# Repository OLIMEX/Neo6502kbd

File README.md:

# Neo6502kbd
Neo6502kbd is all in one Retro computer with 6502 processor, Keyboard, Four USB hosts and DVI/HDMI output.

With Reload emulator you can run Apple ][ and Oric Atmos emulators.

[Neo6502kbd-1](DOCUMENTS/Neo6502kbd-1.jpg)

https://www.olimex.com/Products/Retro-Computers/Neo6502kbd/open-source-hardware

## Licensee
* Hardware is released under CERN Open Hardware Licence Version 2 - Strongly Reciprocal
* Software is released under MIT Licensee
* Documentation is released under CC BY-SA 4.!

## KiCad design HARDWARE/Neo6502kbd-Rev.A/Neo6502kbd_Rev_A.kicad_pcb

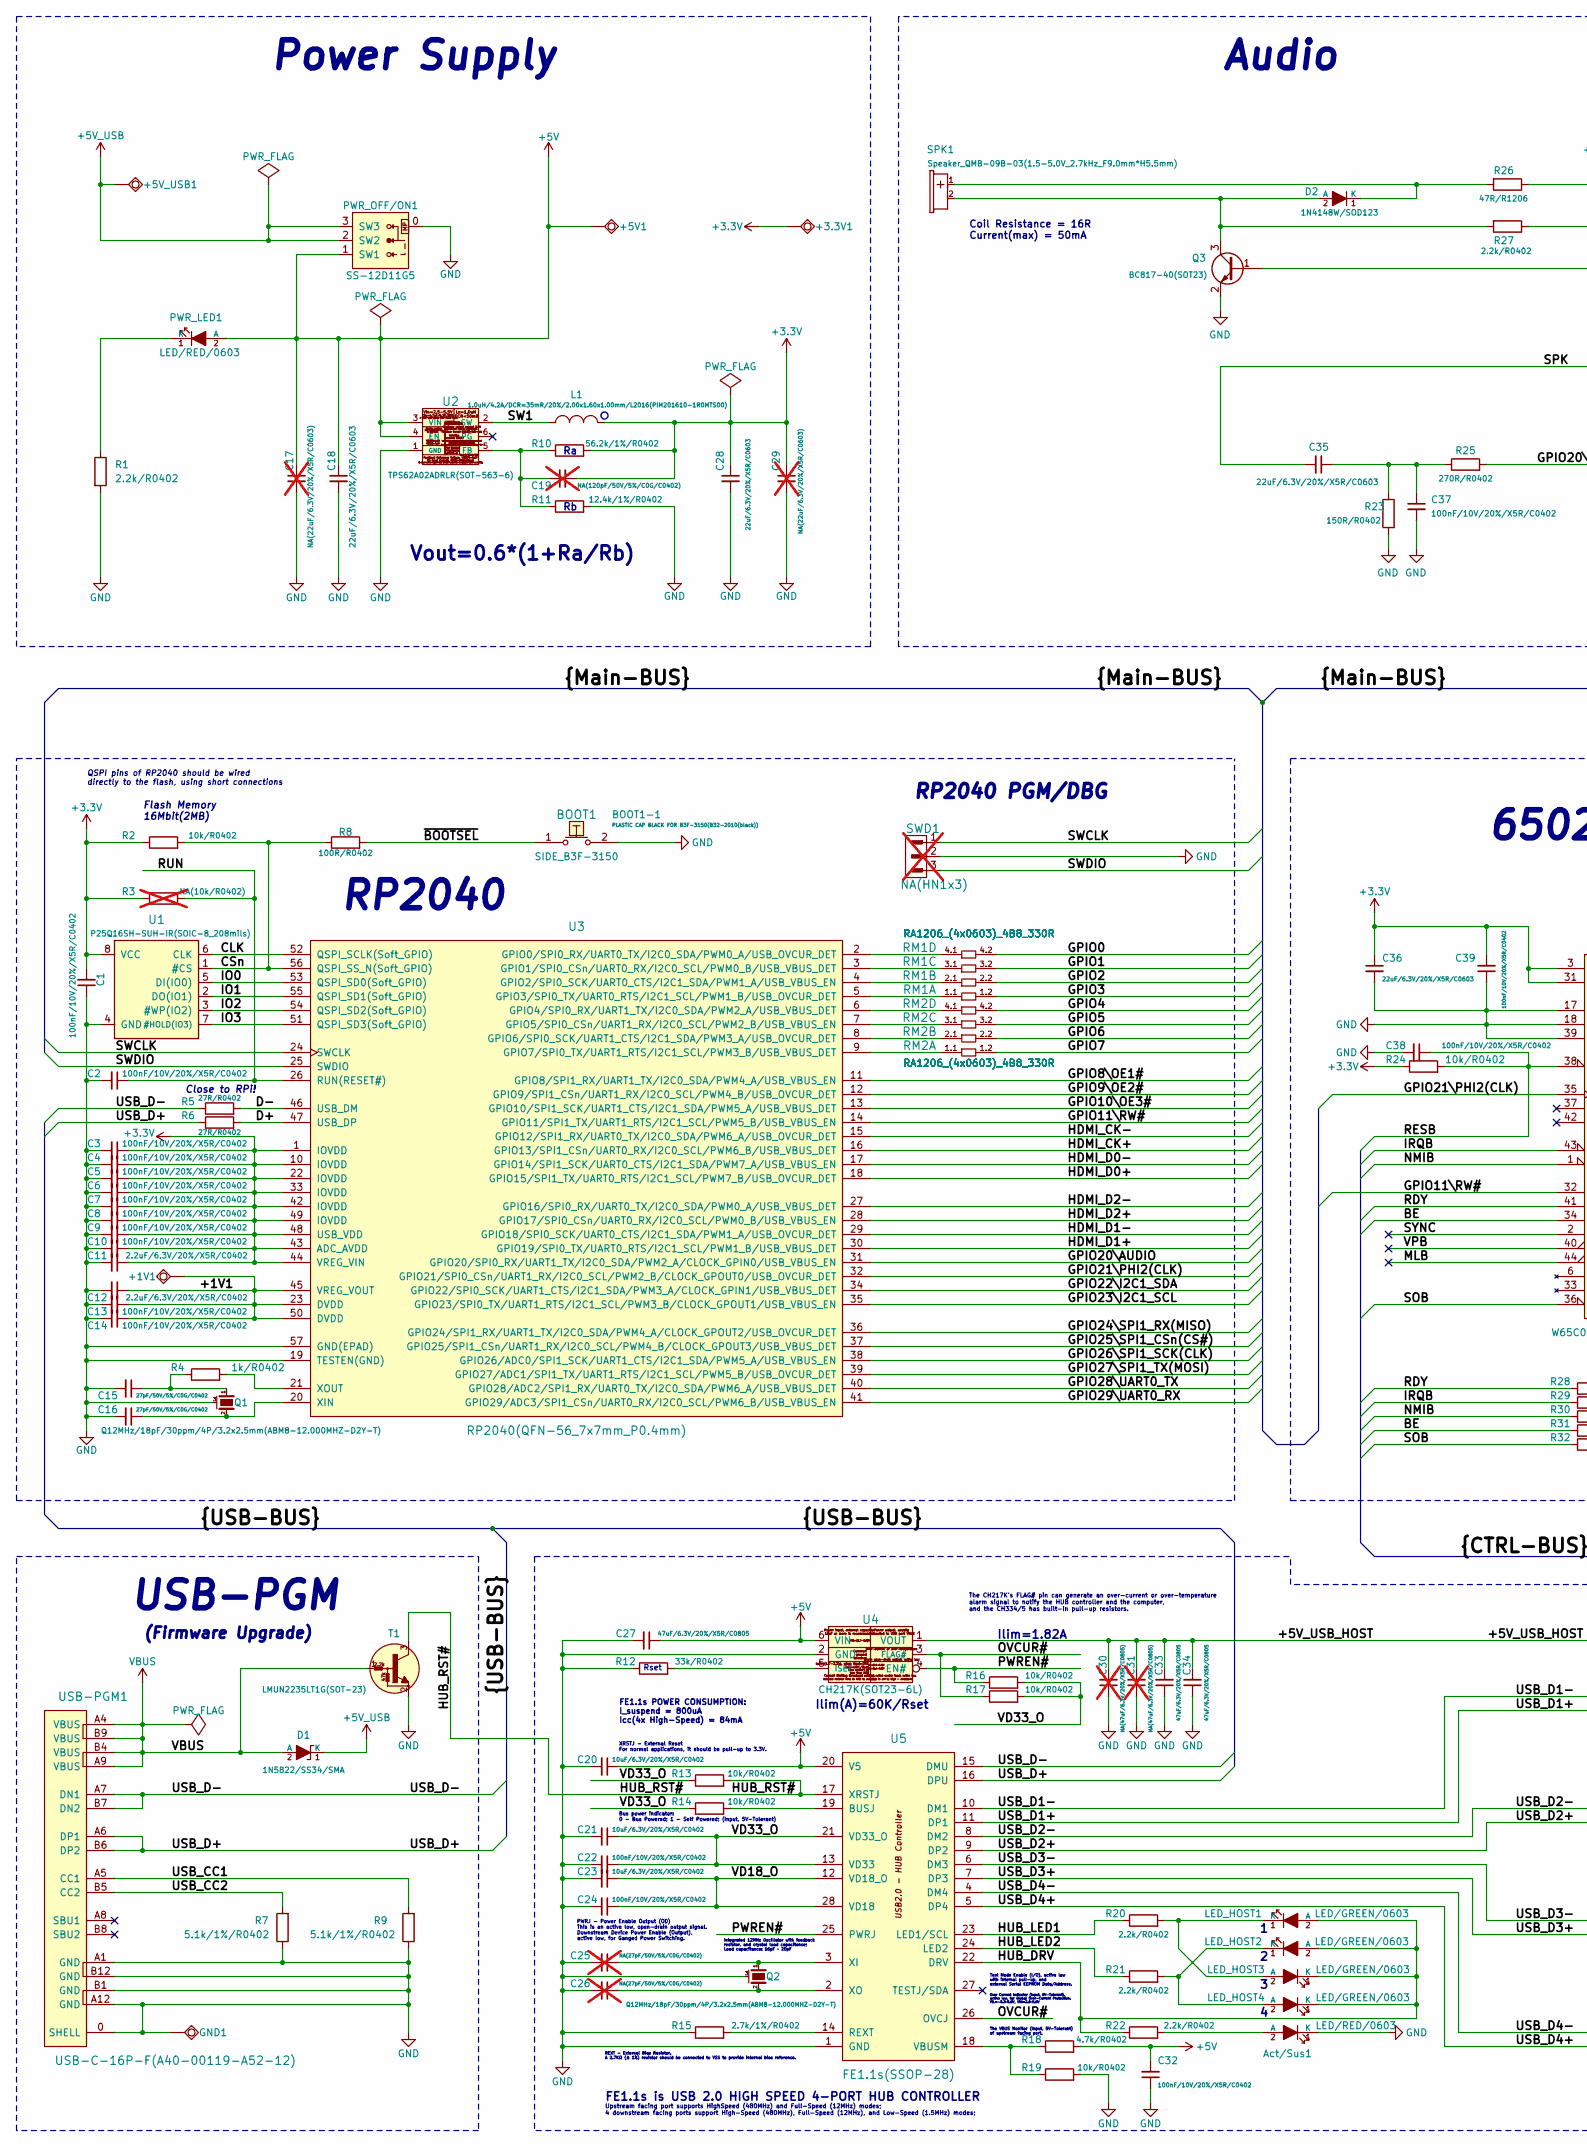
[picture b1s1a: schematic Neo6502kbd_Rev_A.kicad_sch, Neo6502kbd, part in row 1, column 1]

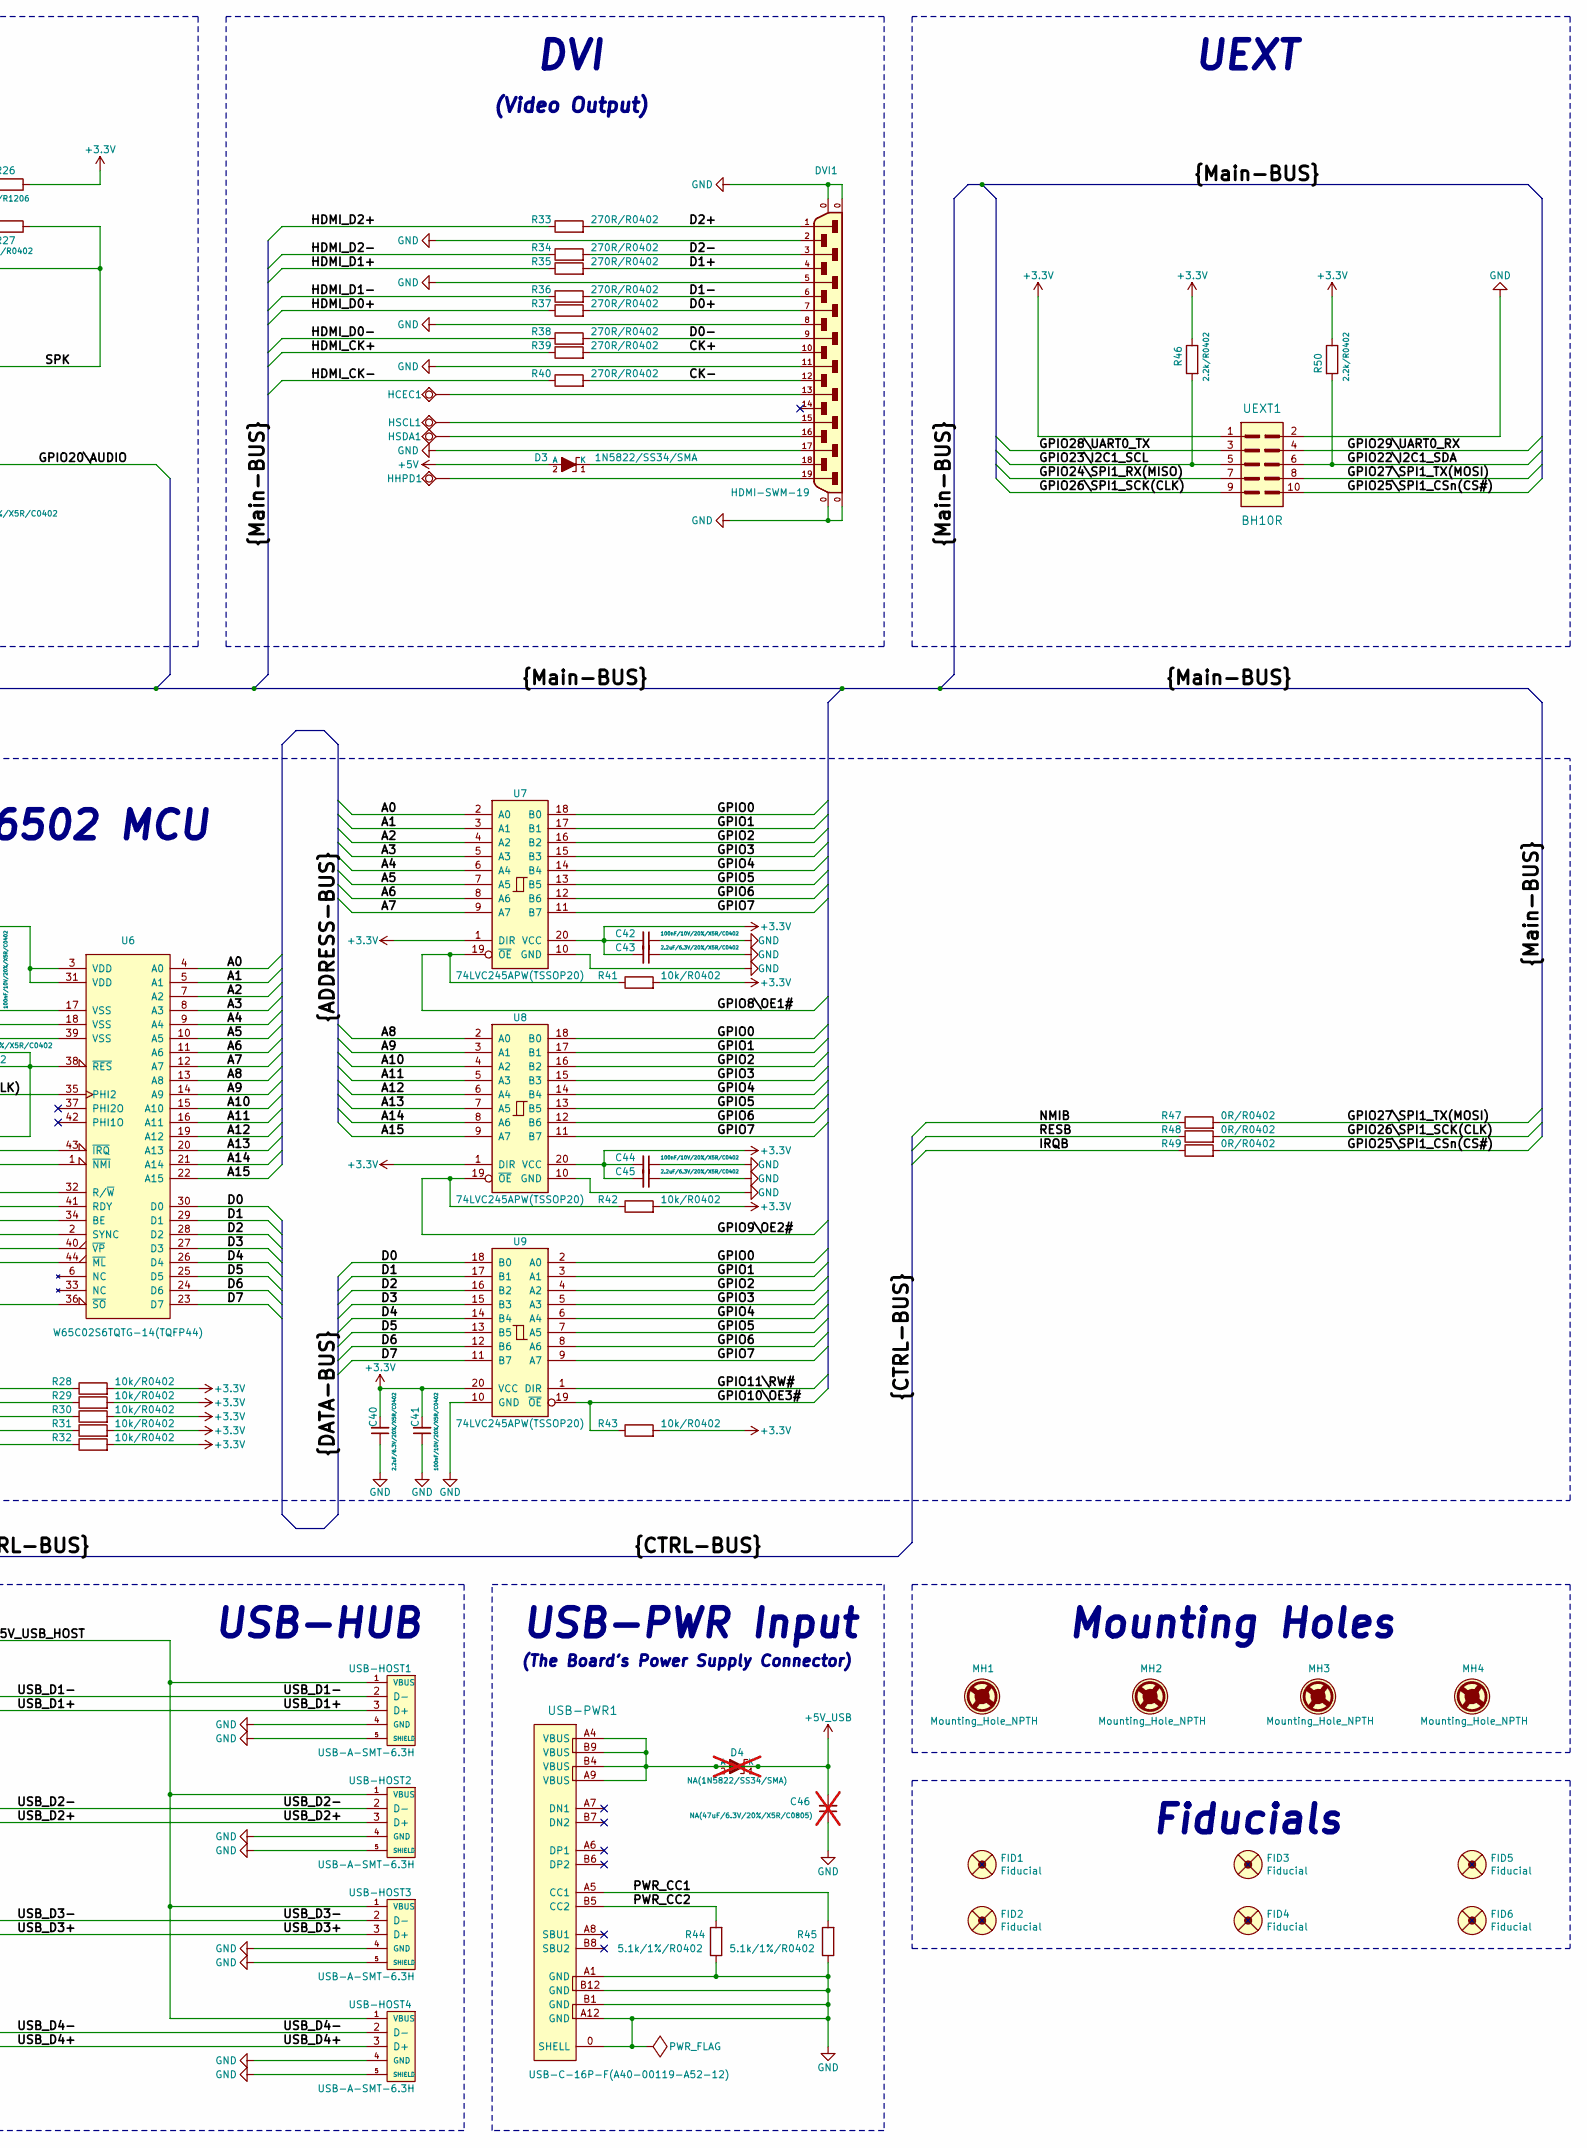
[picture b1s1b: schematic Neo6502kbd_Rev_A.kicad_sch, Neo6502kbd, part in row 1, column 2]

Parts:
+1V1, +3.3V1, +5V1, +5V_USB1: TESTPAD; TEST_PAD40x70_SQUARE
Act/Sus1: LED/RED/0603; LED_0603_KA
BOOT1: SIDE_B3F-3150; B3F-31XX
BOOT1-1: PLASTIC CAP BLACK FOR B3F-3150(B32-2010(black)); BUT-CAP_B32-2010(black)
C1, C2, C3, C4, C5, C6, C7, C8, C9, C10, C13, C14, C22, C24, C32, C37, C38, C39, C41, C42, C44: 100nF/10V/20%/X5R/C0402; C_0402_5MIL_DWS
C11, C12, C40, C43, C45: 2.2uF/6.3V/20%/X5R/C0402; C_0402_5MIL_DWS
C15, C16: 27pF/50V/5%/C0G/C0402; C_0402_5MIL_DWS
C17, C29: NA(22uF/6.3V/20%/X5R/C0603); C_0603_5MIL_DWS; not fitted
C18, C28, C35, C36: 22uF/6.3V/20%/X5R/C0603; C_0603_5MIL_DWS
C19: NA(120pF/50V/5%/C0G/C0402); C_0402_5MIL_DWS; not fitted
C20, C21, C23: 10uF/6.3V/20%/X5R/C0402; C_0402_5MIL_DWS
C25, C26: NA(27pF/50V/5%/C0G/C0402); C_0402_5MIL_DWS; not fitted
C27, C33, C34: 47uF/6.3V/20%/X5R/C0805; C_0805_5MIL_DWS
C30, C31, C46: NA(47uF/6.3V/20%/X5R/C0805); C_0805_5MIL_DWS; not fitted
D1, D3: 1N5822/SS34/SMA; SMA-KA
D2: 1N4148W/SOD123; SOD-123_1C-2A_KA
D4: NA(1N5822/SS34/SMA); SMA-KA; not fitted
DVI1: HDMI-SWM-19; HDMI-SWM-19_Paste
FID1, FID2, FID3: Fiducial; Fiducial1x3_Paste
FID4, FID5, FID6: Fiducial; Fiducial1x3
GND1: TESTPAD; TEST_PAD40x70_SQUARE
HCEC1: TESTPAD; TESTPAD_40-ROUND
HHPD1: TESTPAD; TESTPAD_40-ROUND
HSCL1: TESTPAD; TESTPAD_40-ROUND
HSDA1: TESTPAD; TESTPAD_40-ROUND
L1: 1.0uH/4.2A/DCR=35mR/20%/2.00x1.60x1.00mm/L2016(PI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; L_2016_MM
LED_HOST1, LED_HOST2, LED_HOST3, LED_HOST4: LED/GREEN/0603; LED_0603_KA
MH1, MH2, MH3, MH4: Mounting_Hole_NPTH; Mounting_Hole_Drill-3.3mm_Clerance-7mm
PWR_LED1: LED/RED/0603; LED_0603_KA
PWR_OFF/ON1: SS-12D11G5
Q1, Q2: Q12MHz/18pF/30ppm/4P/3.2x2.5mm(ABM8-12.000MHZ-D2Y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; TSX-3.2x2.5mm_GND(3)
Q3: BC817-40(SOT23); SOT23
R1, R20, R21, R22, R27, R46, R50: 2.2k/R0402; R_0402_5MIL_DWS
R2, R13, R14, R16, R17, R19, R24, R28, R29, R30, R31, R32, R41, R42, R43: 10k/R0402; R_0402_5MIL_DWS
R3: NA(10k/R0402); R_0402_5MIL_DWS; not fitted
R4: 1k/R0402; R_0402_5MIL_DWS
R5, R6: 27R/R0402; R_0402_5MIL_DWS
R7, R9, R44, R45: 5.1k/1%/R0402; R_0402_5MIL_DWS
R8: 100R/R0402; R_0402_5MIL_DWS
R10: 56.2k/1%/R0402; R_0402_5MIL_DWS
R11: 12.4k/1%/R0402; R_0402_5MIL_DWS
R12: 33k/R0402; R_0402_5MIL_DWS
R15: 2.7k/1%/R0402; R_0402_5MIL_DWS
R18: 4.7k/R0402; R_0402_5MIL_DWS
R23: 150R/R0402; R_0402_5MIL_DWS
R25, R33, R34, R35, R36, R37, R38, R39, R40: 270R/R0402; R_0402_5MIL_DWS
R26: 47R/R1206; R_1206_5MIL_DWS
R47, R48, R49: 0R/R0402; R_0402_5MIL_DWS
RM1, RM2: RA1206_(4x0603)_4B8_330R; RA1206_(4X0603)_4B8_xx
SPK1: Speaker_QMB-09B-03(1.5-5.0V_2.7kHz_F9.0mm*H5.5mm); Speaker_QMB-09B-03_1-Plus_2-Minus
SWD1: NA(HN1x3); HN1x3; not fitted
T1: LMUN2235LT1G(SOT-23); SOT23
U1: P25Q16SH-SUH-IR(SOIC-8_208mils); SO-8_208mil
U2: TPS62A02ADRLR(SOT-563-6); SOT-563-6
U3: RP2040(QFN-56_7x7mm_P0.4mm); QFN56_7x7_Pitch_0.4mm
U4: CH217K(SOT23-6L); SOT23-6
U5: FE1.1s(SSOP-28); SSOP28_10x4mm_Pitch_0.64mm
U6: W65C02S6TQTG-14(TQFP44); TQFP44_NEO6502
U7, U8, U9: 74LVC245APW(TSSOP20); TSSOP20_Pitch-0.65mm_6.6x4.5x1.2mm
UEXT1: BH10R
USB-HOST1, USB-HOST2, USB-HOST3, USB-HOST4: USB-A-SMT-6.3H; USB-A-SMT-6.3H_HOST_Female
USB-PGM1: USB-C-16P-F(A40-00119-A52-12); USB2.0_TYPE-C(A40-00119-A52-12)_Paste
USB-PWR1: USB-C-16P-F(A40-00119-A52-12); USB2.0_TYPE-C(A40-00119-A52-12)_Paste

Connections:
+3.3V: +3.3V1.1 (Pad), C1.2, C3.1, C4.1, C5.1, C6.1, C7.1, C8.1, C9.1, C10.1, C11.1, C19.2, C28.1, C29.1, C36.1, C39.2, C40.2, C41.2, C42.2, C43.2, C44.2, C45.2, L1.2, R2.1, R3.1, R10.2, R24.1, R26.1, R28.2, R29.2, R30.2, R31.2, R32.2, R41.2, R42.2, R43.2, R46.1, R50.1, U1.8 (VCC), U3.1 (IOVDD), U3.10 (IOVDD), U3.22 (IOVDD), U3.33 (IOVDD), U3.42 (IOVDD), U3.43 (ADC_AVDD), U3.44 (VREG_VIN), U3.48 (USB_VDD), U3.49 (IOVDD), U6.3 (VDD), U6.31 (VDD), U7.1 (DIR), U7.20 (VCC), U8.1 (DIR), U8.20 (VCC), U9.20 (VCC), UEXT1.1
+5V: +5V1.1 (Pad), C17.1, C18.1, C20.1, C27.1, C32.2, D3.2 (A), PWR_LED1.2 (A), PWR_OFF/ON1.1 (SW1), R18.2, U2.3 (VIN), U2.4 (EN), U4.6 (VIN), U5.20 (V5)
+5V_USB: +5V_USB1.1 (Pad), C46.2, D1.1 (K), D4.1 (K), D4.2 (A), PWR_OFF/ON1.2 (SW2), PWR_OFF/ON1.3 (SW3), USB-PWR1.A4 (VBUS), USB-PWR1.A9 (VBUS), USB-PWR1.B4 (VBUS), USB-PWR1.B9 (VBUS)
/+1V1: +1V1.1 (Pad), C12.1, C13.1, C14.1, U3.23 (DVDD), U3.45 (VREG_VOUT), U3.50 (DVDD)
/+5V_USB_HOST: C30.2, C31.2, C33.2, C34.2, U4.1 (VOUT), USB-HOST1.1 (VBUS), USB-HOST2.1 (VBUS), USB-HOST3.1 (VBUS), USB-HOST4.1 (VBUS)
/A0: U6.4 (A0), U7.2 (A0)
/A1: U6.5 (A1), U7.3 (A1)
/A2: U6.7 (A2), U7.4 (A2)
/A3: U6.8 (A3), U7.5 (A3)
/A4: U6.9 (A4), U7.6 (A4)
/A5: U6.10 (A5), U7.7 (A5)
/A6: U6.11 (A6), U7.8 (A6)
/A7: U6.12 (A7), U7.9 (A7)
/A8: U6.13 (A8), U8.2 (A0)
/A9: U6.14 (A9), U8.3 (A1)
/A10: U6.15 (A10), U8.4 (A2)
/A11: U6.16 (A11), U8.5 (A3)
/A12: U6.19 (A12), U8.6 (A4)
/A13: U6.20 (A13), U8.7 (A5)
/A14: U6.21 (A14), U8.8 (A6)
/A15: U6.22 (A15), U8.9 (A7)
/BE: R31.1, U6.34 (BE)
/CK+: DVI1.10, R39.2
/CK-: DVI1.12, R40.2
/CLK: U1.6 (CLK), U3.52 (QSPI_SCLK(Soft_GPIO))
/CSn: R2.2, R8.1, U1.1 (#CS), U3.56 (QSPI_SS_N(Soft_GPIO))
/D0: U6.30 (D0), U9.18 (B0)
/D0+: DVI1.7, R37.2
/D0-: DVI1.9, R38.2
/D1: U6.29 (D1), U9.17 (B1)
/D1+: DVI1.4, R35.2
/D1-: DVI1.6, R36.2
/D2: U6.28 (D2), U9.16 (B2)
/D2+: DVI1.1, R33.2
/D2-: DVI1.3, R34.2
/D3: U6.27 (D3), U9.15 (B3)
/D4: U6.26 (D4), U9.14 (B4)
/D5: U6.25 (D5), U9.13 (B5)
/D6: U6.24 (D6), U9.12 (B6)
/D7: U6.23 (D7), U9.11 (B7)
/D+: R6.2, U3.47 (USB_DP)
/D-: R5.2, U3.46 (USB_DM)
/GPIO0: RM1.4.2, U7.18 (B0), U8.18 (B0), U9.2 (A0)
/GPIO1: RM1.3.2, U7.17 (B1), U8.17 (B1), U9.3 (A1)
/GPIO2: RM1.2.2, U7.16 (B2), U8.16 (B2), U9.4 (A2)
/GPIO3: RM1.1.2, U7.15 (B3), U8.15 (B3), U9.5 (A3)
/GPIO4: RM2.4.2, U7.14 (B4), U8.14 (B4), U9.6 (A4)
/GPIO5: RM2.3.2, U7.13 (B5), U8.13 (B5), U9.7 (A5)
/GPIO6: RM2.2.2, U7.12 (B6), U8.12 (B6), U9.8 (A6)
/GPIO7: RM2.1.2, U7.11 (B7), U8.11 (B7), U9.9 (A7)
/GPIO8\OE1#: R41.1, U3.11 (GPIO8/SPI1_RX/UART1_TX/I2C0_SDA/PWM4_A/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), U7.19 (~OE)
/GPIO9\OE2#: R42.1, U3.12 (GPIO9/SPI1_CSn/UART1_RX/I2C0_SCL/PWM4_B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), U8.19 (~OE)
/GPIO10\OE3#: R43.1, U3.13 (GPIO10/SPI1_SCK/UART1_CTS/I2C1_SDA/PWM5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), U9.19 (~OE)
/GPIO11\RW#: U3.14 (GPIO11/SPI1_TX/UART1_RTS/I2C1_SCL/PWM5_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), U6.32 (R/~W), U9.1 (DIR)
/GPIO20\AUDIO: R25.2, U3.31 (GPIO20/SPI0_RX/UART1_TX/I2C0_SDA/PWM2_A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)
/GPIO21\PHI2(CLK): U3.32 (GPIO21/SPI0_CSn/UART1_RX/I2C0_SCL/PWM2_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), U6.35 (PHI2)
/GPIO22\I2C1_SDA: R50.2, U3.34 (GPIO22/SPI0_SCK/UART1_CTS/I2C1_SDA/PWM3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), UEXT1.6
/GPIO23\I2C1_SCL: R46.2, U3.35 (GPIO23/SPI0_TX/UART1_RTS/I2C1_SCL/PWM3_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), UEXT1.5
/GPIO24\SPI1_RX(MISO): U3.36 (GPIO24/SPI1_RX/UART1_TX/I2C0_SDA/PWM4_A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), UEXT1.7
/GPIO25\SPI1_CSn(CS#): R49.2, U3.37 (GPIO25/SPI1_CSn/UART1_RX/I2C0_SCL/PWM4_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), UEXT1.10
/GPIO26\SPI1_SCK(CLK): R48.2, U3.38 (GPIO26/ADC0/SPI1_SCK/UART1_CTS/I2C1_SDA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), UEXT1.9
/GPIO27\SPI1_TX(MOSI): R47.2, U3.39 (GPIO27/ADC1/SPI1_TX/UART1_RTS/I2C1_SCL/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), UEXT1.8
/GPIO28\UART0_TX: U3.40 (GPIO28/ADC2/SPI1_RX/UART0_TX/I2C0_SDA/P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), UEXT1.3
/GPIO29\UART0_RX: U3.41 (GPIO29/ADC3/SPI1_CSn/UART0_RX/I2C0_SCL/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), UEXT1.4
/HDMI_CK+: R39.1, U3.16 (GPIO13/SPI1_CSn/UART0_RX/I2C0_SCL/PWM6_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)
/HDMI_CK-: R40.1, U3.15 (GPIO12/SPI1_RX/UART0_TX/I2C0_SDA/PWM6_A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)
/HDMI_D0+: R37.1, U3.18 (GPIO15/SPI1_TX/UART0_RTS/I2C1_SCL/PWM7_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)
/HDMI_D0-: R38.1, U3.17 (GPIO14/SPI1_SCK/UART0_CTS/I2C1_SDA/PWM7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)
/HDMI_D1+: R35.1, U3.30 (GPIO19/SPI0_TX/UART0_RTS/I2C1_SCL/PWM1_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)
/HDMI_D1-: R36.1, U3.29 (GPIO18/SPI0_SCK/UART0_CTS/I2C1_SDA/PWM1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)
/HDMI_D2+: R33.1, U3.28 (GPIO17/SPI0_CSn/UART0_RX/I2C0_SCL/PWM0_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)
/HDMI_D2-: R34.1, U3.27 (GPIO16/SPI0_RX/UART0_TX/I2C0_SDA/PWM0_A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)
/HUB_DRV: LED_HOST1.2 (A), LED_HOST2.2 (A), LED_HOST3.1 (K), LED_HOST4.1 (K), R22.1, U5.22 (DRV)
/HUB_LED1: R20.1, U5.23 (LED1/SCL)
/HUB_LED2: R21.1, U5.24 (LED2)
/HUB_RST#: R13.2, T1.3 (C), U5.17 (XRSTJ)
/IO0: U1.5 (DI(IO0)), U3.53 (QSPI_SD0(Soft_GPIO))
/IO1: U1.2 (DO(IO1)), U3.55 (QSPI_SD1(Soft_GPIO))
/IO2: U1.3 (#WP(IO2)), U3.54 (QSPI_SD2(Soft_GPIO))
/IO3: U1.7 (#HOLD(IO3)), U3.51 (QSPI_SD3(Soft_GPIO))
/IRQB: R29.1, R49.1, U6.43 (~IRQ)
/MLB: U6.44 (~ML)
/NMIB: R30.1, R47.1, U6.1 (~NMI)
/OVCUR#: R17.1, U4.3 (FLAG#), U5.26 (OVCJ)
/PWREN#: R16.1, U4.4 (EN#), U5.25 (PWRJ)
/PWR_CC1: R45.2, USB-PWR1.A5 (CC1)
/PWR_CC2: R44.2, USB-PWR1.B5 (CC2)
/RDY: R28.1, U6.41 (RDY)
/RESB: C38.1, R24.2, R48.1, U6.38 (~RES)
/RUN: C2.1, R3.2, U3.26 (RUN(RESET#))
/SOB: R32.1, U6.36 (~SO)
/SPK: C35.2, Q3.1 (B), R27.1
/SW1: L1.1, U2.2 (SW)
/SWCLK: SWD1.1, U3.24 (SWCLK)
/SWDIO: SWD1.3, U3.25 (SWDIO)
/SYNC: U6.2 (SYNC)
/USB_CC1: R9.2, USB-PGM1.A5 (CC1)
/USB_CC2: R7.2, USB-PGM1.B5 (CC2)
/USB_D1+: U5.11 (DP1), USB-HOST1.3 (D+)
/USB_D1-: U5.10 (DM1), USB-HOST1.2 (D-)
/USB_D2+: U5.9 (DP2), USB-HOST2.3 (D+)
/USB_D2-: U5.8 (DM2), USB-HOST2.2 (D-)
/USB_D3+: U5.7 (DP3), USB-HOST3.3 (D+)
/USB_D3-: U5.6 (DM3), USB-HOST3.2 (D-)
/USB_D4+: U5.5 (DP4), USB-HOST4.3 (D+)
/USB_D4-: U5.4 (DM4), USB-HOST4.2 (D-)
/USB_D+: R6.1, U5.16 (DPU), USB-PGM1.A6 (DP1), USB-PGM1.B6 (DP2)
/USB_D-: R5.1, U5.15 (DMU), USB-PGM1.A7 (DN1), USB-PGM1.B7 (DN2)
/VD18_O: C23.1, C24.1, U5.12 (VD18_O), U5.28 (VD18)
/VD33_O: C21.1, C22.1, R13.1, R14.1, R16.2, R17.2, U5.13 (VD33), U5.21 (VD33_O)
/VPB: U6.40 (~VP)
/~BOOTSEL: BOOT1.1, R8.2
GND: Act/Sus1.1 (K), BOOT1.2, C1.1, C2.2, C3.2, C4.2, C5.2, C6.2, C7.2, C8.2, C9.2, C10.2, C11.2, C12.2, C13.2, C14.2, C15.2, C16.2, C17.2, C18.2, C20.2, C21.2, C22.2, C23.2, C24.2, C25.2, C26.2, C27.2, C28.2, C29.2, C30.1, C31.1, C32.1, C33.1, C34.1, C36.2, C37.2, C38.2, C39.1, C40.1, C41.1, C42.1, C43.1, C44.1, C45.1, C46.1, DVI1.0 (23), DVI1.2, DVI1.5, DVI1.8, DVI1.11, DVI1.17, GND1.1 (Pad), PWR_OFF/ON1.0, Q1.3 (case), Q2.3 (case), Q3.2 (E), R1.2, R7.1, R9.1, R11.2, R12.1, R15.1, R19.2, R23.2, R44.1, R45.1, SWD1.2, T1.2 (E), U1.4 (GND), U2.1 (GND), U3.19 (TESTEN(GND)), U3.57 (GND(EPAD)), U4.2 (GND), U5.1 (GND), U6.17 (VSS), U6.18 (VSS), U6.39 (VSS), U7.10 (GND), U8.10 (GND), U9.10 (GND), UEXT1.2, USB-HOST1.4 (GND), USB-HOST1.5 (SHIELD), USB-HOST2.4 (GND), USB-HOST2.5 (SHIELD), USB-HOST3.4 (GND), USB-HOST3.5 (SHIELD), USB-HOST4.4 (GND), USB-HOST4.5 (SHIELD), USB-PGM1.0 (SHELL), USB-PGM1.A1 (GND), USB-PGM1.A12 (GND), USB-PGM1.B1 (GND), USB-PGM1.B12 (GND), USB-PWR1.0 (SHELL), USB-PWR1.A1 (GND), USB-PWR1.A12 (GND), USB-PWR1.B1 (GND), USB-PWR1.B12 (GND)
unnamed: Act/Sus1.2 (A), R22.2
unnamed: C15.1, Q1.1, R4.1
unnamed: C35.1, C37.1, R23.1, R25.1
unnamed: D2.2 (A), Q3.3 (C), R27.2, SPK1.2 (MINUS)
unnamed: D2.1 (K), R26.2, SPK1.1 (PLUS)
unnamed: D3.1 (K), DVI1.18
unnamed: DVI1.13, HCEC1.1 (Pad)
unnamed: DVI1.15, HSCL1.1 (Pad)
unnamed: DVI1.16, HSDA1.1 (Pad)
unnamed: DVI1.19, HHPD1.1 (Pad)
unnamed: LED_HOST1.1 (K), LED_HOST3.2 (A), R20.2
unnamed: LED_HOST2.1 (K), LED_HOST4.2 (A), R21.2
unnamed: PWR_LED1.1 (K), R1.1
unnamed: C19.1, R10.1, R11.1, U2.5 (FB)
unnamed: RM1.4.1, U3.2 (GPIO0/SPI0_RX/UART0_TX/I2C0_SDA/PWM0_A/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)
unnamed: RM1.3.1, U3.3 (GPIO1/SPI0_CSn/UART0_RX/I2C0_SCL/PWM0_B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)
unnamed: RM1.2.1, U3.4 (GPIO2/SPI0_SCK/UART0_CTS/I2C1_SDA/PWM1_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)
unnamed: RM1.1.1, U3.5 (GPIO3/SPI0_TX/UART0_RTS/I2C1_SCL/PWM1_B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)
unnamed: RM2.4.1, U3.6 (GPIO4/SPI0_RX/UART1_TX/I2C0_SDA/PWM2_A/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)
unnamed: RM2.3.1, U3.7 (GPIO5/SPI0_CSn/UART1_RX/I2C0_SCL/PWM2_B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)
unnamed: RM2.2.1, U3.8 (GPIO6/SPI0_SCK/UART1_CTS/I2C1_SDA/PWM3_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)
unnamed: RM2.1.1, U3.9 (GPIO7/SPI0_TX/UART1_RTS/I2C1_SCL/PWM3_B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)
unnamed: C16.1, Q1.2, U3.20 (XIN)
unnamed: R4.2, U3.21 (XOUT)
unnamed: R12.2, U4.5 (ISET)
unnamed: R14.2, U5.19 (BUSJ)
unnamed: R15.2, U5.14 (REXT)
unnamed: R18.1, R19.1, U5.18 (VBUSM)
unnamed: C25.1, Q2.1, U5.3 (XI)
unnamed: C26.1, Q2.2, U5.2 (XO)
VBUS: D1.2 (A), T1.1 (B), USB-PGM1.A4 (VBUS), USB-PGM1.A9 (VBUS), USB-PGM1.B4 (VBUS), USB-PGM1.B9 (VBUS)

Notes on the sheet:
USB-PWR Input
The VBUS Monitor (Input, 5V-Tolerant) of upstream facing port.
The CH217K's FLAG# pin can generate an over-current or over-temperature alarm signal to notify the HUB controller and the computer, and the CH334/5 has built-in pull-up resistors.
(The Board's Power Supply Connector)
QSPI pins of RP2040 should be wired directly to the flash, using short connections
USB-HUB
Integrated 12MHz Oscillator with feedback resistor, and crystal load capacitance; Load capacitance: 16pF ~ 20pF
(Video Output)
6502 MCU
Rset
Upstream facing port supports HighSpeed (480MHz) and Full-Speed (12MHz) modes; 4 downstream facing ports support High-Speed (480MHz), Full-Speed (12MHz), and Low-Speed (1.5MHz) modes;
(Firmware Upgrade)
XRSTJ - External Reset For normal applications, it should be pull-up to 3.3V.
Close to RPi!
Coil Resistance = 16R Current(max) = 50mA
USB-PGM
UEXT
FE1.1s POWER CONSUMPTION: I_suspend = 800uA Icc(4x High-Speed) = 84mA
Mounting Holes
REXT - External Bias Resistor. A 2.7KΩ (± 1%) resistor should be connected to VSS to provide internal bias reference.
FE1.1s is USB 2.0 HIGH SPEED 4-PORT HUB CONTROLLER
Ilim(A)=60K/Rset
Fiducials
Audio
Bus power indicator: 0 - Bus Powered; 1 - Self Powered; (Input, 5V-Tolerant)
Ilim=1.82A
RP2040 PGM/DBG
DVI
Over Current Indicator (Input, 5V-Tolerant), active low, for Global Over-Current Protection. VIL=-0.3~0.8V, VIH=2.0~5.5V
RP2040
PWRJ - Power Enable Output (OD) This is an active low, open-drain output signal. Downstream Device Power Enable (Output), active low, for Ganged Power Switching.
Power Supply
Vout=0.6*(1+Ra/Rb)
Test Mode Enable (I/O), active low with internal pull-up, and external Serial EEPROM Data/Address.
Flash Memory 16Mbit(2MB)

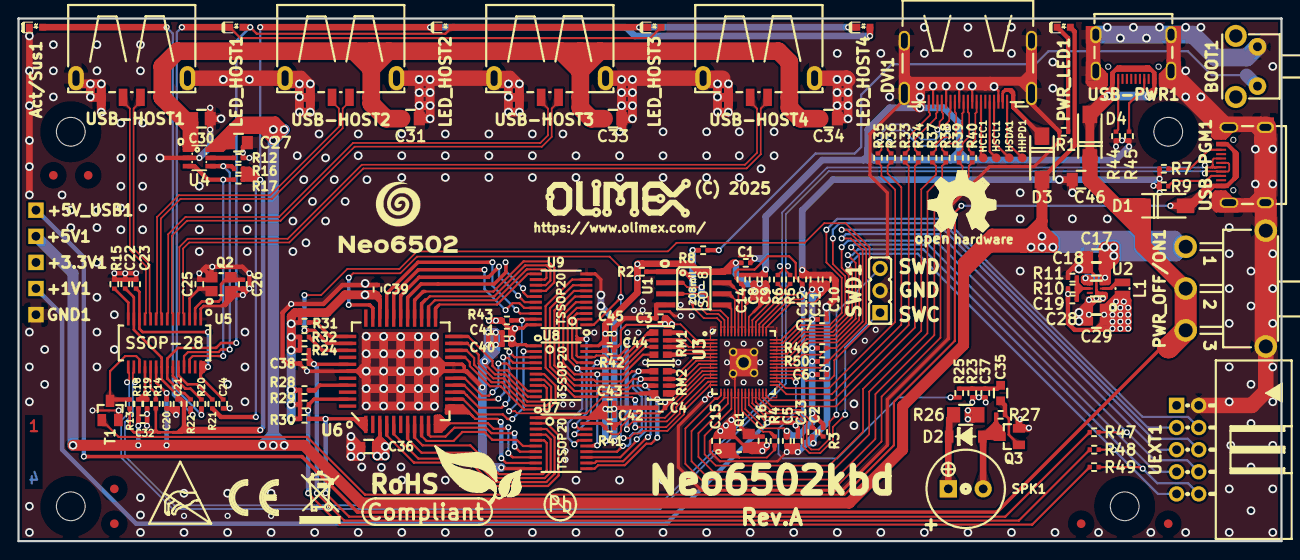
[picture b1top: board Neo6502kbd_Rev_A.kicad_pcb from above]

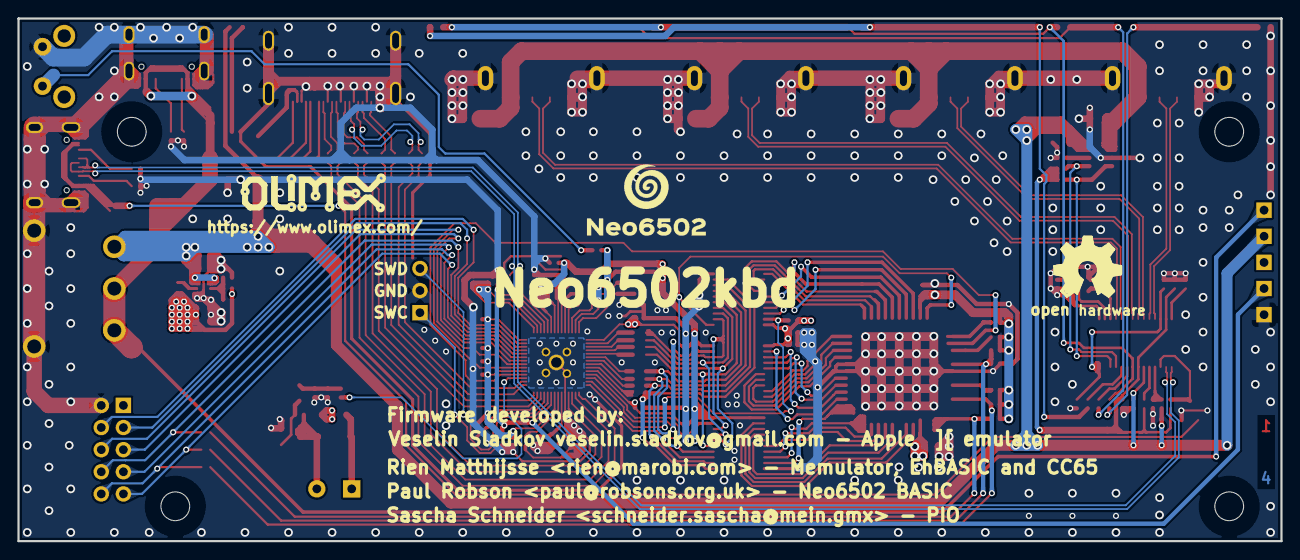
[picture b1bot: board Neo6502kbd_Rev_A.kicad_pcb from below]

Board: 4 copper layers, 145.0 x 60.0 mm, 165 parts (7 on the bottom side), 141 nets.

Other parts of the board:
Logo_OLIMEX_TB-Bottom: Logo_OLIMEX_TB
Logo_OLIMEX_TB-Top: Logo_OLIMEX_TB
NEO_LOGO_SMALL*: LOGO; Neo6502_Sign_Small
NEO_LOGO_SMALL-Top: LOGO; Neo6502_Sign_Small
Sign_Antistatic: Sign_Antistatic
Sign_CE: CE_Sign
Sign_OSHW_8x8, Sign_OSHW_8x8-Top: Sign_OSHW_8x8
Sign_PB-Free: Sign_PB-Free
Sign_RecycleBin: Sign_RecycleBin; Sign_RecycleBin_1
Sign_RoHS: Sign_RoHS; Sign_RoHS_1

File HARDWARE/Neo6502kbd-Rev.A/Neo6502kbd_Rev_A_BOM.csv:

Quantity,Value,Footprint,Reference
2,LED/RED/0603,LED_0603_KA,"Act/Sus1, PWR_LED1"
1,SIDE_B3F-3150,B3F-31XX,BOOT1
1,PLASTIC CAP BLACK FOR B3F-3150(B32-2010(black)),BUT-CAP_B32-2010(black),BOOT1-1
21,100nF/10V/20%/X5R/C0402,C_0402_5MIL_DWS,"C1, C2, C3, C4, C5, C6, C7, C8, C9, C10, C13, C14, C22, C24, C32, C37, C38, C39, C41, C42, C44"
5,2.2uF/6.3V/20%/X5R/C0402,C_0402_5MIL_DWS,"C11, C12, C40, C43, C45"
2,27pF/50V/5%/C0G/C0402,C_0402_5MIL_DWS,"C15, C16"
4,22uF/6.3V/20%/X5R/C0603,C_0603_5MIL_DWS,"C18, C28, C35, C36"
3,10uF/6.3V/20%/X5R/C0402,C_0402_5MIL_DWS,"C20, C21, C23"
3,47uF/6.3V/20%/X5R/C0805,C_0805_5MIL_DWS,"C27, C33, C34"
2,1N5822/SS34/SMA,SMA-KA,"D1, D3"
1,1N4148W/SOD123,SOD-123_1C-2A_KA,D2
1,HDMI-SWM-19,HDMI-SWM-19_Paste,DVI1
1,1.0uH/4.2A/DCR=35mR/20%/2.00x1.60x1.00mm/L2016(PIM201610-1R0MTS00),L_2016_MM,L1
4,LED/GREEN/0603,LED_0603_KA,"LED_HOST1, LED_HOST2, LED_HOST3, LED_HOST4"
1,SS-12D11G5,SS-12D11G5,PWR_OFF/ON1
2,Q12MHz/18pF/30ppm/4P/3.2x2.5mm(ABM8-12.000MHZ-D2Y-T),TSX-3.2x2.5mm_GND(3),"Q1, Q2"
1,BC817-40(SOT23),SOT23,Q3
7,2.2k/R0402,R_0402_5MIL_DWS,"R1, R20, R21, R22, R27, R46, R50"
15,10k/R0402,R_0402_5MIL_DWS,"R2, R13, R14, R16, R17, R19, R24, R28, R29, R30, R31, R32, R41, R42, R43"
1,1k/R0402,R_0402_5MIL_DWS,R4
2,27R/R0402,R_0402_5MIL_DWS,"R5, R6"
4,5.1k/1%/R0402,R_0402_5MIL_DWS,"R7, R9, R44, R45"
1,100R/R0402,R_0402_5MIL_DWS,R8
1,56.2k/1%/R0402,R_0402_5MIL_DWS,R10
1,12.4k/1%/R0402,R_0402_5MIL_DWS,R11
1,33k/R0402,R_0402_5MIL_DWS,R12
1,2.7k/1%/R0402,R_0402_5MIL_DWS,R15
1,4.7k/R0402,R_0402_5MIL_DWS,R18
1,150R/R0402,R_0402_5MIL_DWS,R23
9,270R/R0402,R_0402_5MIL_DWS,"R25, R33, R34, R35, R36, R37, R38, R39, R40"
1,47R/R1206,R_1206_5MIL_DWS,R26
3,0R/R0402,R_0402_5MIL_DWS,"R47, R48, R49"
2,RA1206_(4x0603)_4B8_330R,RA1206_(4X0603)_4B8_xx,"RM1, RM2"
1,Speaker_QMB-09B-03(1.5-5.0V_2.7kHz_F9.0mm*H5.5mm),Speaker_QMB-09B-03_1-Plus_2-Minus,SPK1
1,LMUN2235LT1G(SOT-23),SOT23,T1
1,P25Q16SH-SUH-IR(SOIC-8_208mils),SO-8_208mil,U1
1,TPS62A02ADRLR(SOT-563-6),SOT-563-6,U2
1,RP2040(QFN-56_7x7mm_P0.4mm),QFN56_7x7_Pitch_0.4mm,U3
1,CH217K(SOT23-6L),SOT23-6,U4
1,FE1.1s(SSOP-28),SSOP28_10x4mm_Pitch_0.64mm,U5
1,W65C02S6TQTG-14(TQFP44),TQFP44_NEO6502,U6
3,74LVC245APW(TSSOP20),TSSOP20_Pitch-0.65mm_6.6x4.5x1.2mm,"U7, U8, U9"
1,BH10R,BH10R,UEXT1
4,USB-A-SMT-6.3H,USB-A-SMT-6.3H_HOST_Female,"USB-HOST1, USB-HOST2, USB-HOST3, USB-HOST4"
2,USB-C-16P-F(A40-00119-A52-12),USB2.0_TYPE-C(A40-00119-A52-12)_Paste,"USB-PGM1, USB-PWR1"

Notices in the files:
HARDWARE/Neo6502kbd-Rev.A/Neo6502kbd_Rev_A.kicad_pcb:
(C) 2025
